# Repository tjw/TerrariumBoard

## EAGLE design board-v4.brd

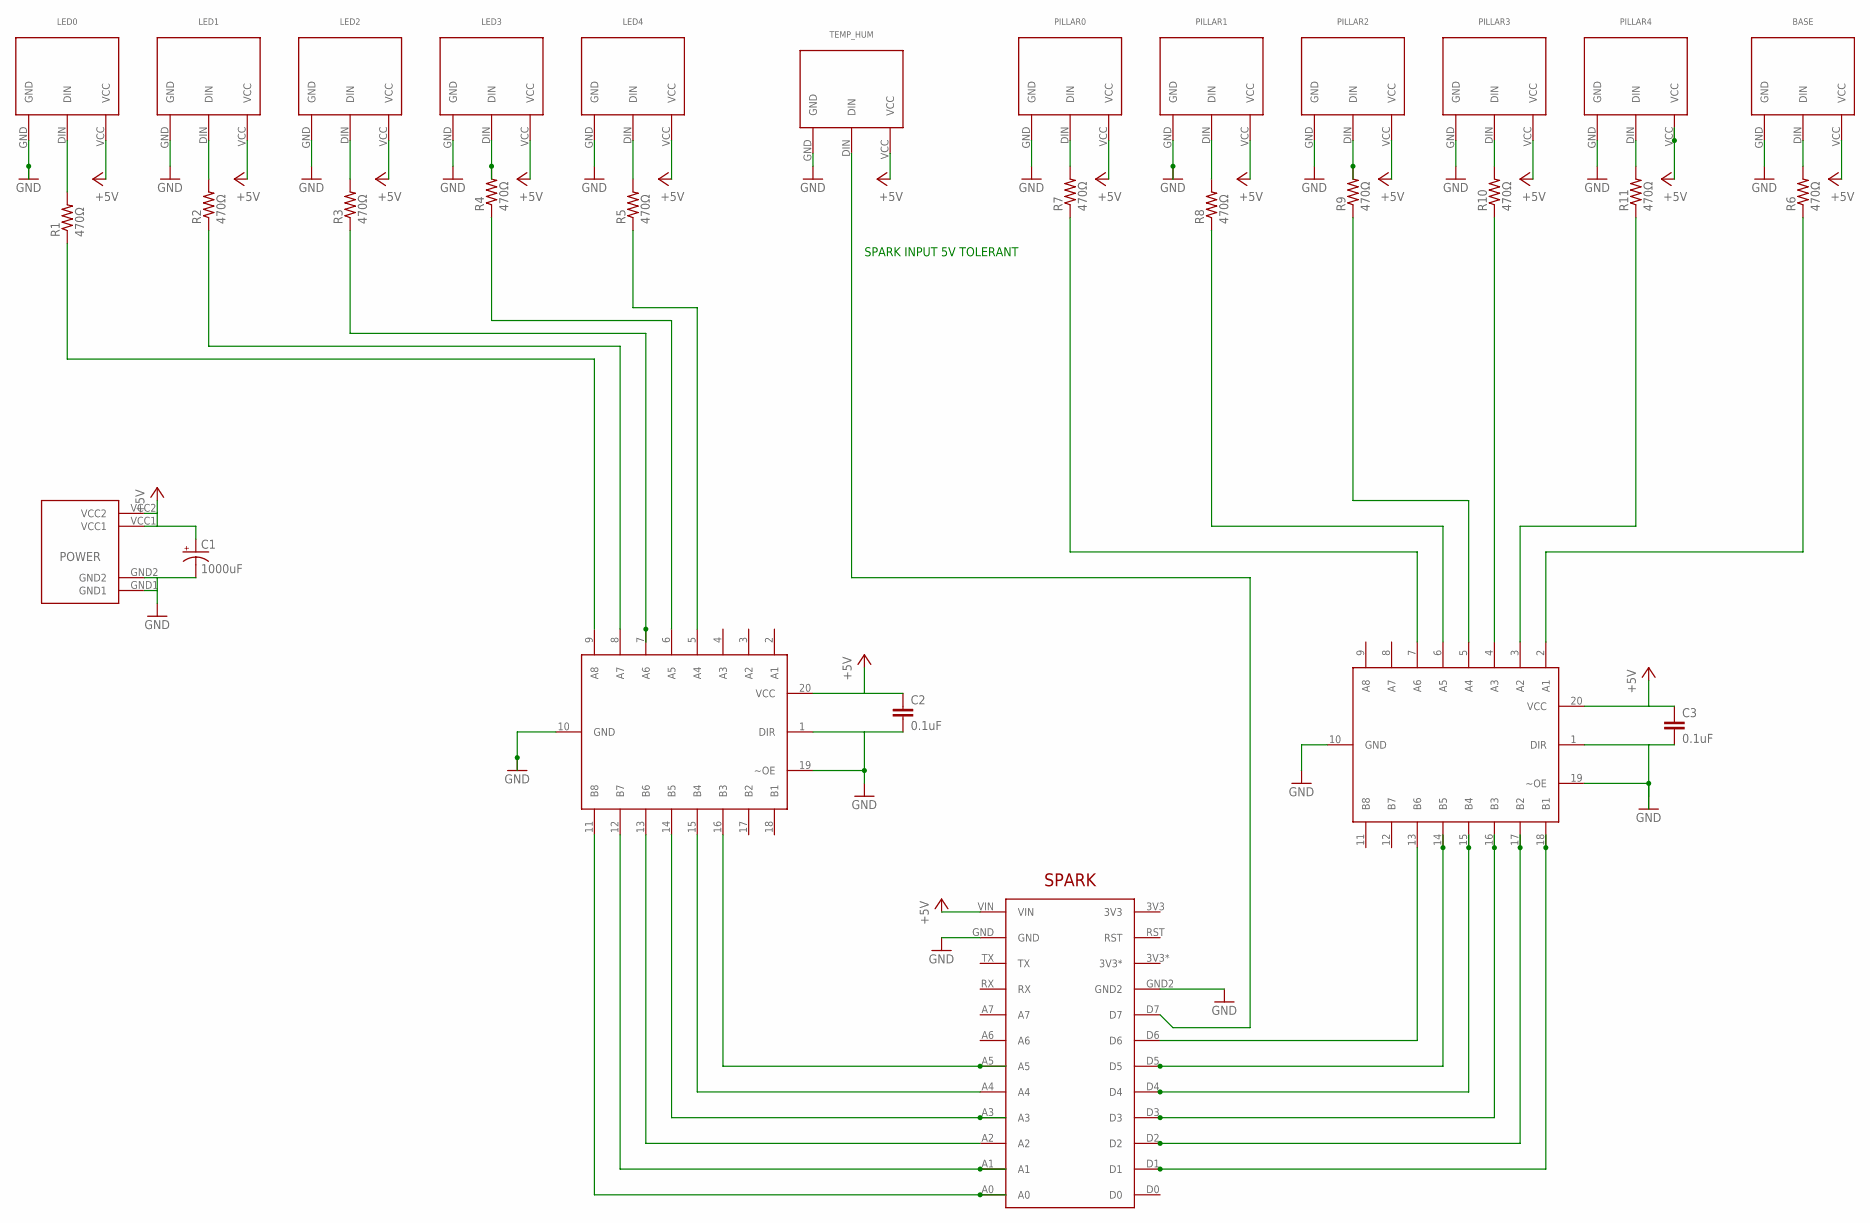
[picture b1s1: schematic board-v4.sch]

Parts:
BASE: MOLEX_3PIN_SMT_43650-310
C1: 1000uF; CPOL-RADIAL-1000UF-25V
C2, C3: 0.1uF; 0805
LED0, LED1, LED2, LED3, LED4: MOLEX_3PIN_SMT_43650-310
PILLAR0, PILLAR1, PILLAR2, PILLAR3, PILLAR4: MOLEX_3PIN_SMT_43650-310
POWER: MOLEX_2PIN_SABRE_POWER
R1, R2, R3, R4, R5, R6, R7, R8, R9, R10, R11: 470Ω; 0805
SHIFT1, SHIFT2: TI_74HCT245DWR; SOIC-20
SPARK: SPARKCORE
TEMP_HUM: MOLEX_3PIN_SMT_43650-310

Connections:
+5V: BASE.VCC, C1.1 (+), C2.1, C3.1, LED0.VCC, LED1.VCC, LED2.VCC, LED3.VCC, LED4.VCC, PILLAR0.VCC, PILLAR1.VCC, PILLAR2.VCC, PILLAR3.VCC, PILLAR4.VCC, POWER.VCC1, POWER.VCC2, SHIFT1.20 (VCC), SHIFT2.20 (VCC), SPARK.VIN, TEMP_HUM.VCC
GND: BASE.GND, C1.2 (-), C2.2, C3.2, LED0.GND, LED1.GND, LED2.GND, LED3.GND, LED4.GND, PILLAR0.GND, PILLAR1.GND, PILLAR2.GND, PILLAR3.GND, PILLAR4.GND, POWER.GND1, POWER.GND2, SHIFT1.1 (DIR), SHIFT1.10 (GND), SHIFT1.19 (~OE), SHIFT2.1 (DIR), SHIFT2.10 (GND), SHIFT2.19 (~OE), SPARK.GND, SPARK.GND2, TEMP_HUM.GND
unnamed: SPARK.D7, TEMP_HUM.DIN
unnamed: SHIFT2.17 (B2), SPARK.D2
unnamed: PILLAR0.DIN, R7.2
unnamed: LED0.DIN, R1.2
unnamed: R1.1, SHIFT1.9 (A8)
unnamed: LED1.DIN, R2.2
unnamed: LED2.DIN, R3.2
unnamed: LED3.DIN, R4.2
unnamed: LED4.DIN, R5.2
unnamed: R6.1, SHIFT2.2 (A1)
unnamed: BASE.DIN, R6.2
unnamed: R11.1, SHIFT2.3 (A2)
unnamed: PILLAR1.DIN, R8.2
unnamed: R10.1, SHIFT2.4 (A3)
unnamed: PILLAR2.DIN, R9.2
unnamed: PILLAR3.DIN, R10.2
unnamed: PILLAR4.DIN, R11.2
unnamed: R2.1, SHIFT1.8 (A7)
unnamed: R3.1, SHIFT1.7 (A6)
unnamed: R4.1, SHIFT1.6 (A5)
unnamed: R5.1, SHIFT1.5 (A4)
unnamed: R9.1, SHIFT2.5 (A4)
unnamed: R8.1, SHIFT2.6 (A5)
unnamed: R7.1, SHIFT2.7 (A6)
unnamed: SHIFT2.13 (B6), SPARK.D6
unnamed: SHIFT2.18 (B1), SPARK.D1
unnamed: SHIFT2.16 (B3), SPARK.D3
unnamed: SHIFT2.14 (B5), SPARK.D5
unnamed: SHIFT2.15 (B4), SPARK.D4
unnamed: SHIFT1.11 (B8), SPARK.A0
unnamed: SHIFT1.12 (B7), SPARK.A1
unnamed: SHIFT1.13 (B6), SPARK.A2
unnamed: SHIFT1.14 (B5), SPARK.A3
unnamed: SHIFT1.15 (B4), SPARK.A4
unnamed: SHIFT1.16 (B3), SPARK.A5

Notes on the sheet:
SPARK INPUT 5V TOLERANT

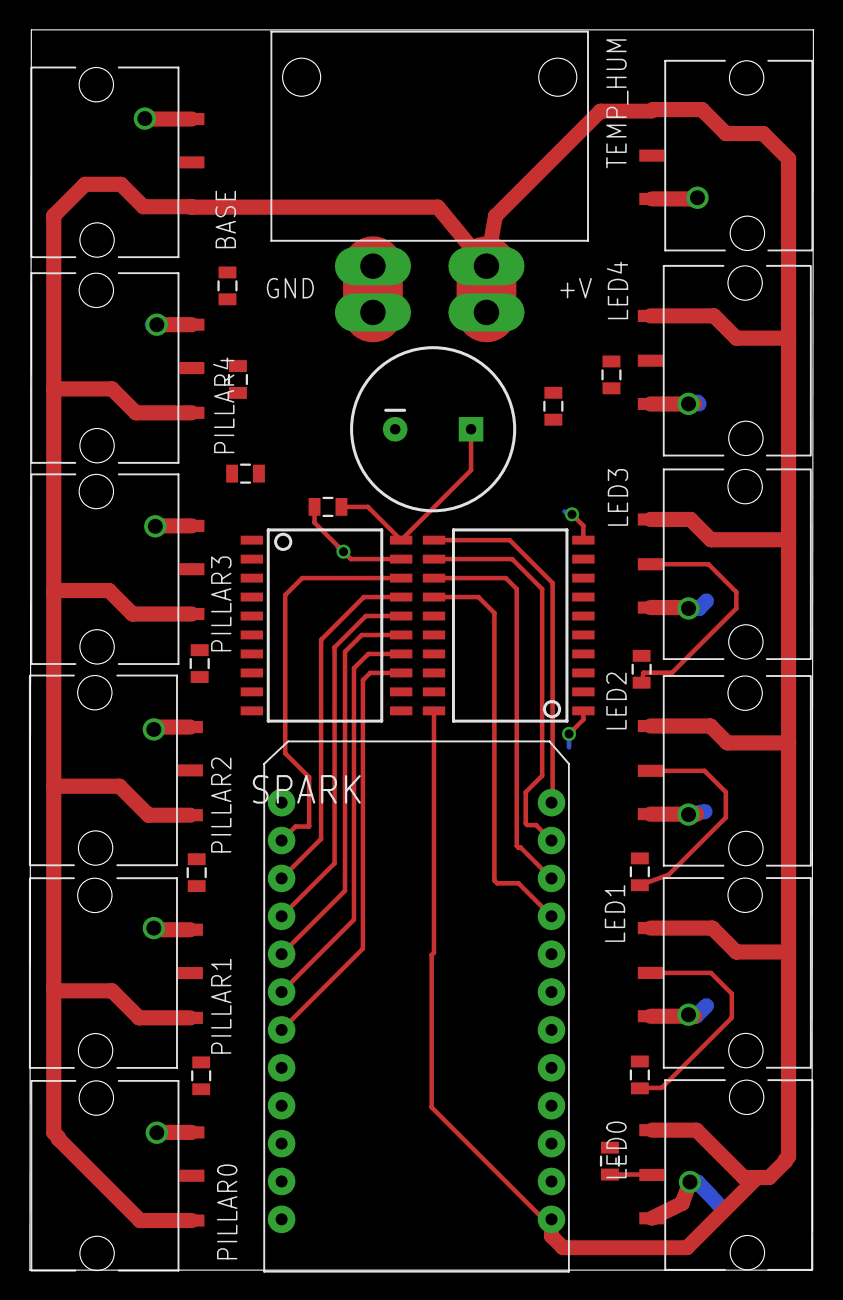
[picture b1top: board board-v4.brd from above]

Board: 2 copper layers, 52.5 x 83.0 mm, 30 parts (0 on the bottom side), 37 nets.

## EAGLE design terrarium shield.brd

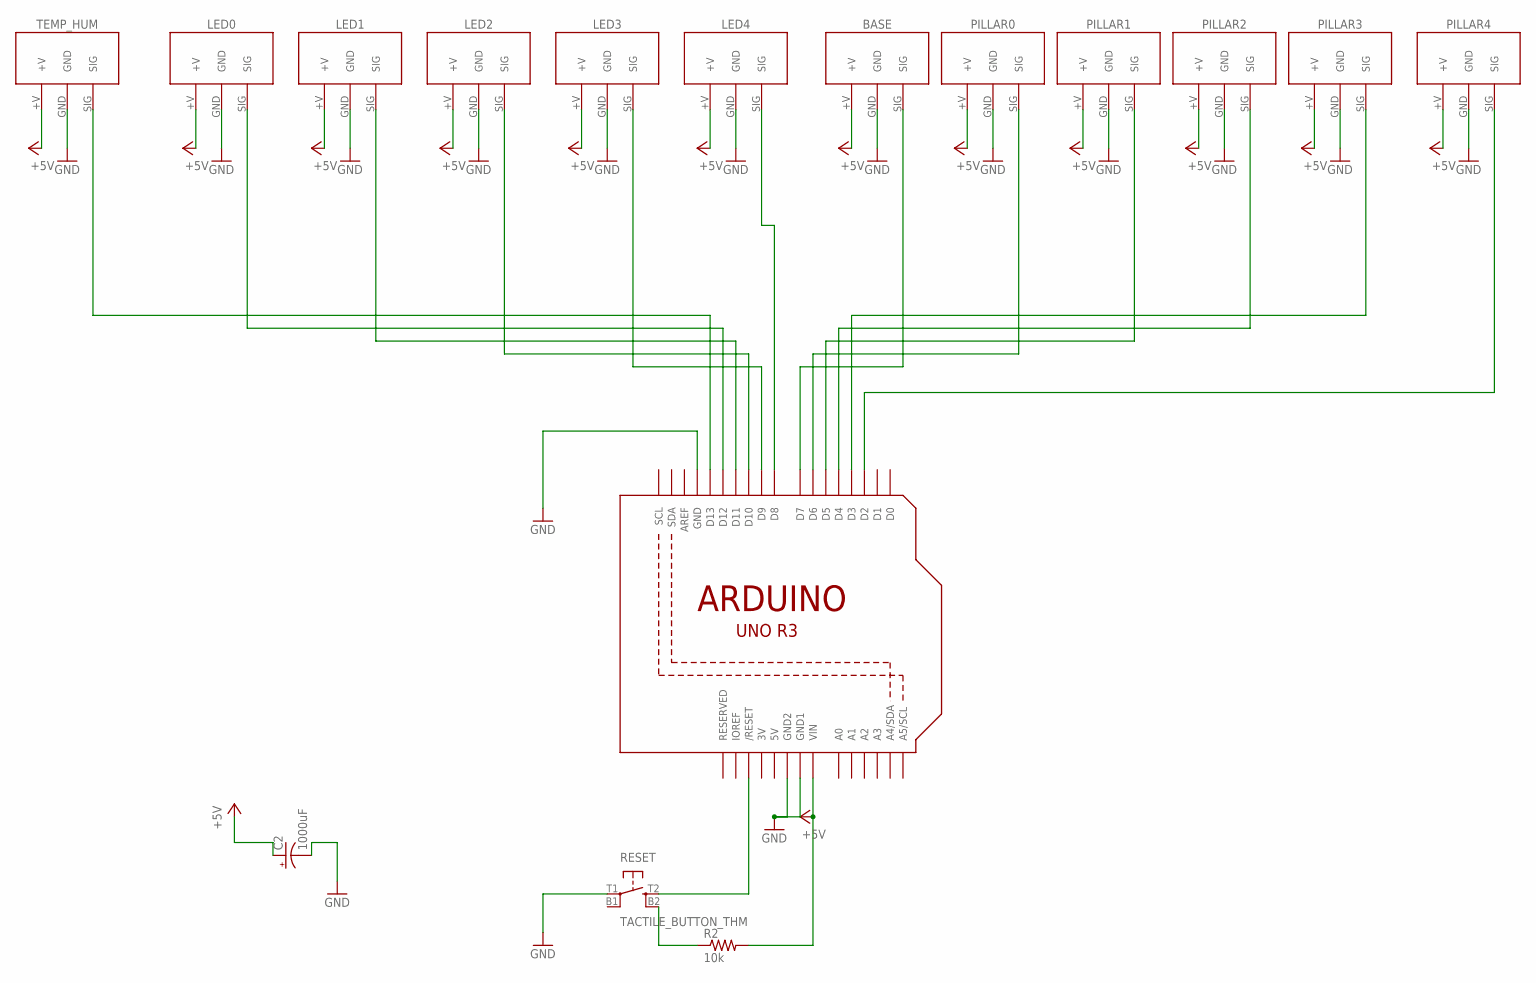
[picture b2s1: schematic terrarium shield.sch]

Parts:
BASE: MOLEX_3PIN_VERT_THM
C2: 1000uF; CPOL-RADIAL-1000UF-25V
LED0, LED1, LED2, LED3, LED4: MOLEX_3PIN_VERT_THM
PILLAR0, PILLAR1, PILLAR2, PILLAR3, PILLAR4: MOLEX_3PIN_VERT_THM
R2: 10k; RESISTOR_THM
RESET: TACTILE_BUTTON_THM
TEMP_HUM: MOLEX_3PIN_VERT_THM
U$1: ARDUINO_UNO_R3

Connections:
3V: U$1.3V
5V: U$1.5V
+5V: BASE.+V, C2.1 (+), LED0.+V, LED1.+V, LED2.+V, LED3.+V, LED4.+V, PILLAR0.+V, PILLAR1.+V, PILLAR2.+V, PILLAR3.+V, PILLAR4.+V, R2.P$2 (2), TEMP_HUM.+V, U$1.VIN
GND: BASE.GND, C2.2 (-), LED0.GND, LED1.GND, LED2.GND, LED3.GND, LED4.GND, PILLAR0.GND, PILLAR1.GND, PILLAR2.GND, PILLAR3.GND, PILLAR4.GND, RESET.T1, TEMP_HUM.GND, U$1.GND, U$1.GND1, U$1.GND2
unnamed: R2.P$1 (1), RESET.B2
unnamed: TEMP_HUM.SIG, U$1.D13
unnamed: LED0.SIG, U$1.D12
unnamed: LED1.SIG, U$1.D11
unnamed: LED2.SIG, U$1.D10
unnamed: LED3.SIG, U$1.D9
unnamed: LED4.SIG, U$1.D8
unnamed: BASE.SIG, U$1.D7
unnamed: PILLAR0.SIG, U$1.D6
unnamed: PILLAR1.SIG, U$1.D5
unnamed: PILLAR2.SIG, U$1.D4
unnamed: PILLAR3.SIG, U$1.D3
unnamed: RESET.T2, U$1.RESET (/RESET)
unnamed: PILLAR4.SIG, U$1.D2

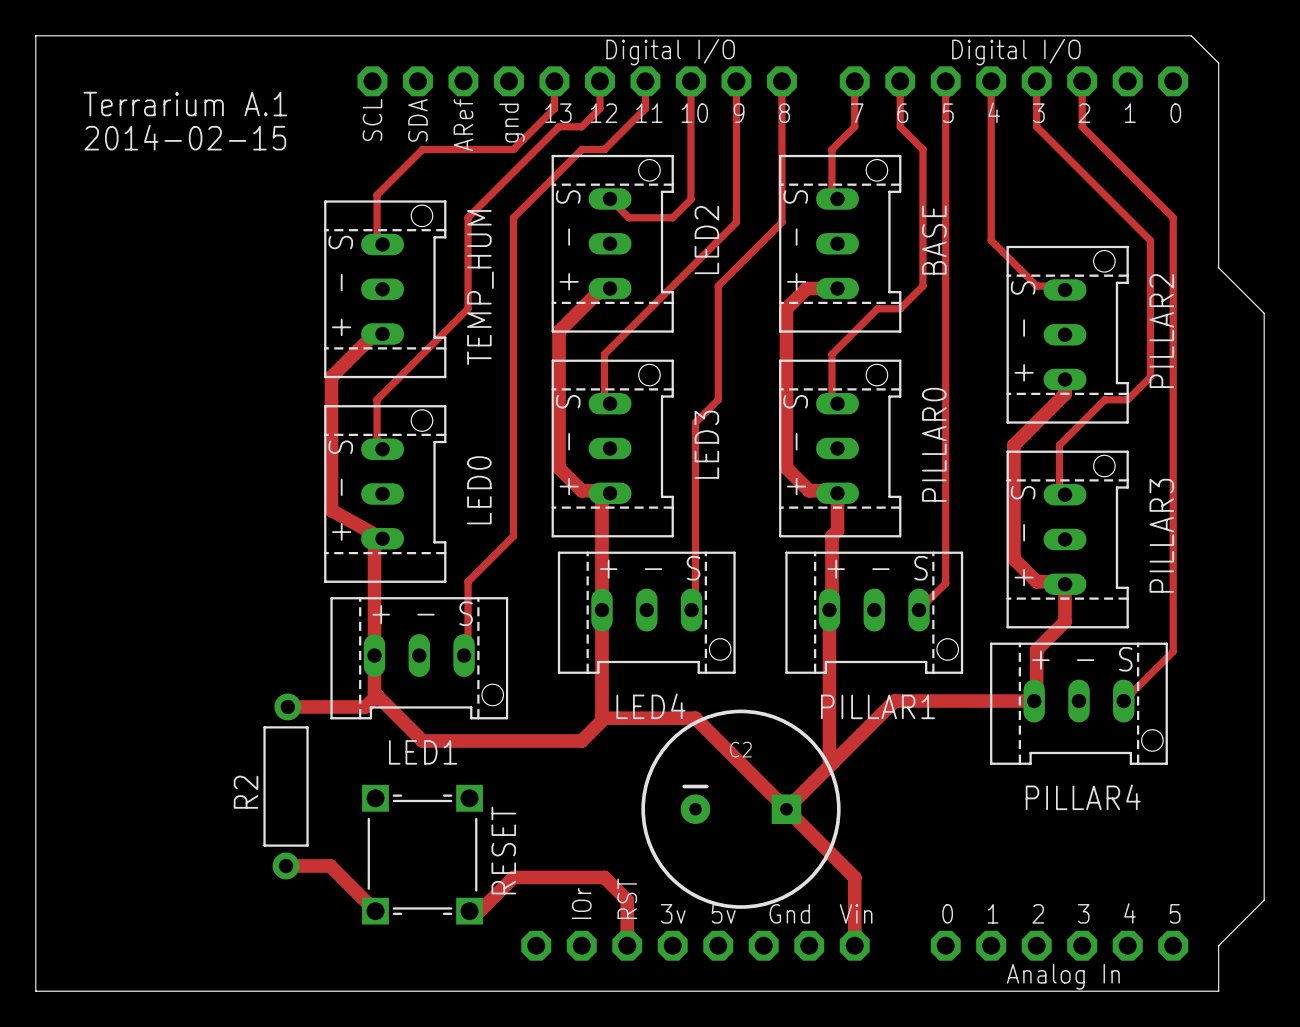
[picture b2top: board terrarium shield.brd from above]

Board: 2 copper layers, 68.6 x 53.3 mm, 16 parts (0 on the bottom side), 16 nets.

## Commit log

2014-02-21 Importing my terrarium shield into git.
2014-02-21 Fix ignore for the Eagle backup version files.
2014-02-21 Current state.
2014-02-25 Some notes from the vA.1 boards I got back.
2014-02-26 Checked electrical connections with meter.
2014-02-26 Connected the other two GND pins to the ground pour.
2014-02-26 Removed DC jack. Will get power from VIN.
2014-02-26 Noting changes. Updated resistor component from library (increased pad size).
2014-02-26 Smashed the capacitor and fixed the name size.
2014-02-26 Added +/-/S markings to connectors. More notes on changes in this rev.
2014-02-26 Move vA.2 to the top of the file and increase version headers to next size up.
2014-03-17 Notes about further fixes, including not making the board smoke...
2014-03-29 WIP on second version.
2014-03-30 Getting ready to send v2 to OSH Park.
2014-03-30 Add a name, version, and date.
2014-03-30 Sadly, pillar0 was touching, but Eagle didn't think it was hooked up.
2014-04-12 Fixed issues from v2.
2014-06-24 New versions.
2014-06-25 Adding source for the controller app and script to flash it via spark.io.
2014-06-25 Updated to build and flash; just runs rainbow across all strips.
2014-06-25 Actually display the intermediate stages.
2014-06-29 Renamed.
2014-06-29 Another mode, remote spark functions, and some notes.
2014-06-29 Simplified app for testing strips.
2014-07-24 Put the bin files for plain builds in a 'builds' directory. Add a 'clean' target.
2014-11-06 Updates to the makefile.

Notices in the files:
parts and their libraries:
SparkFun-Passives: Licensing: CC v3.0 Share-Alike You are welcome to use this library for commercial purposes.
